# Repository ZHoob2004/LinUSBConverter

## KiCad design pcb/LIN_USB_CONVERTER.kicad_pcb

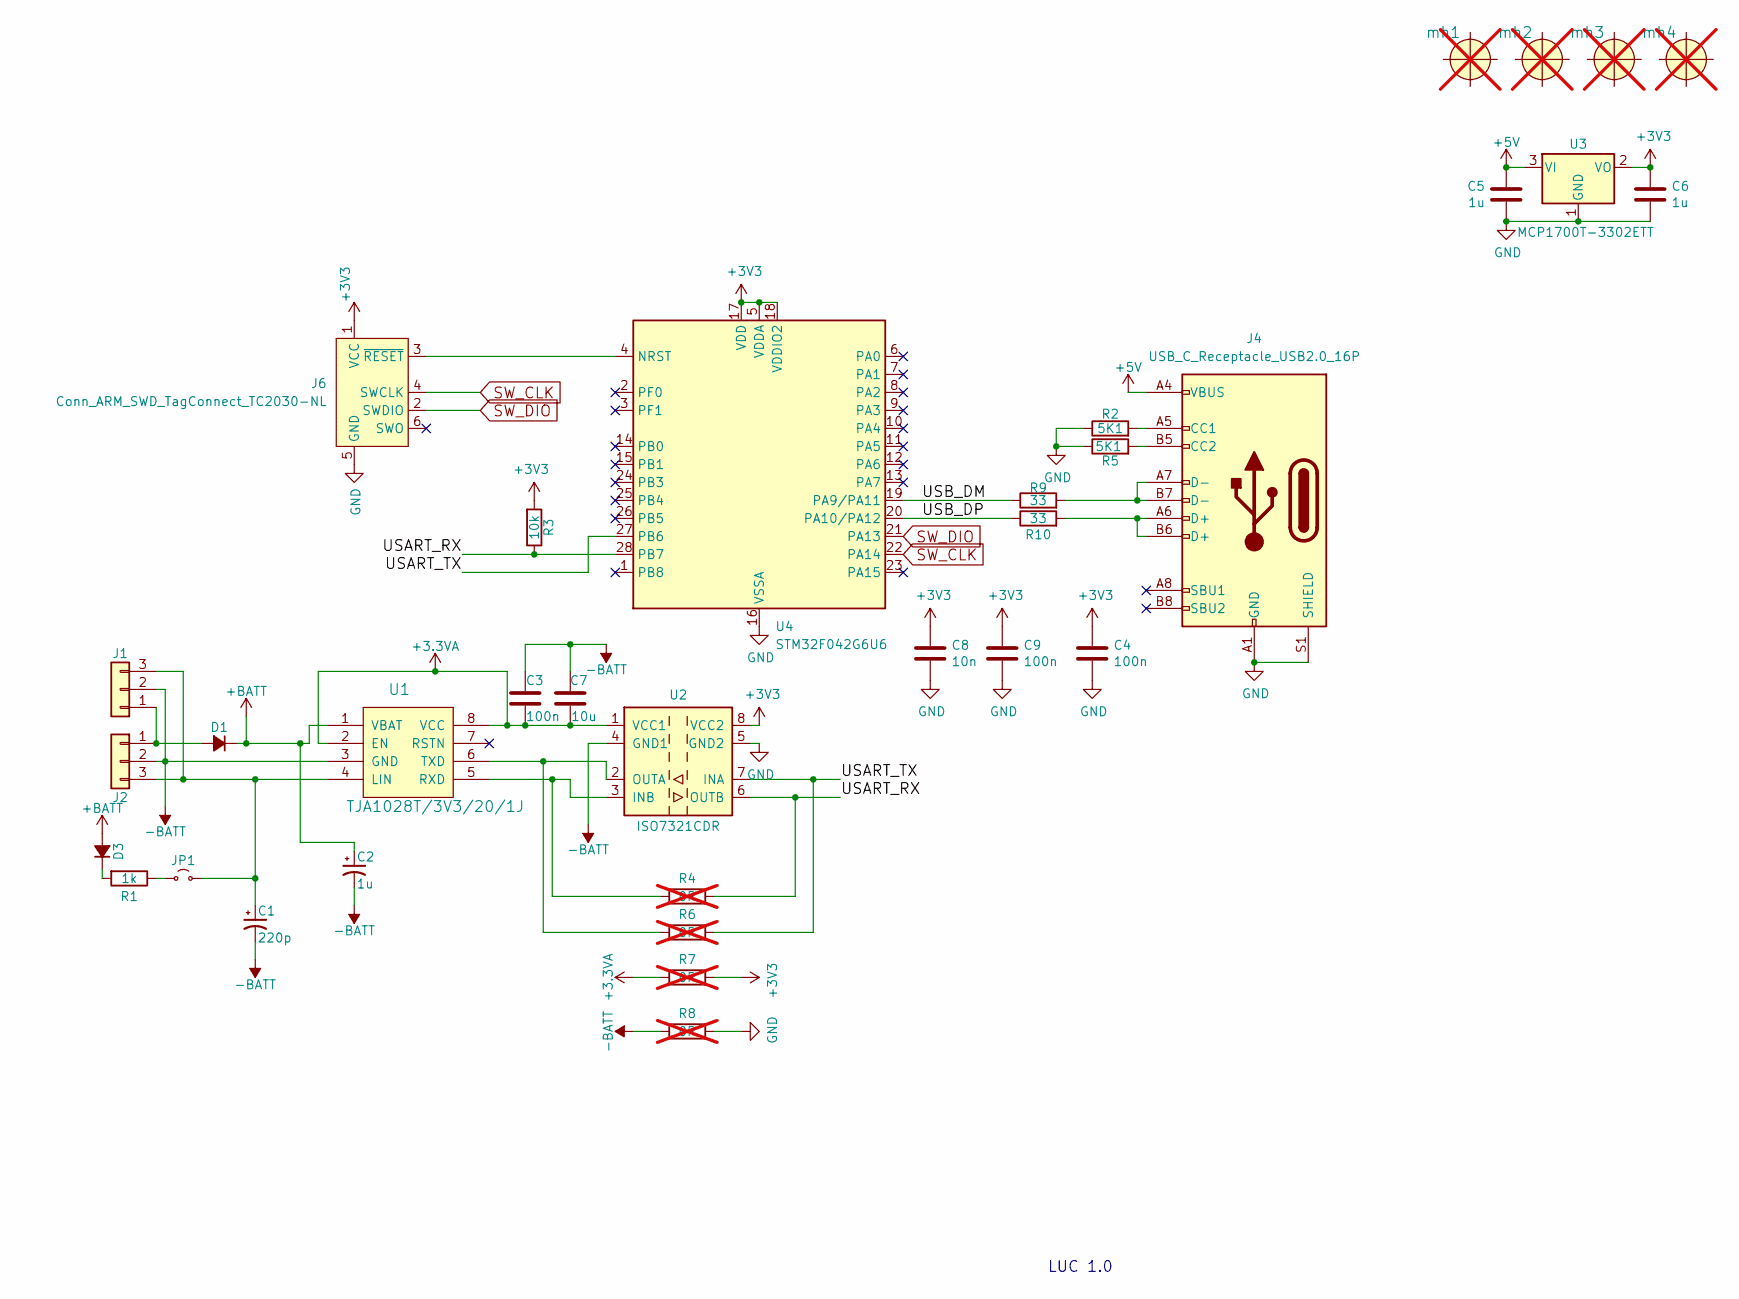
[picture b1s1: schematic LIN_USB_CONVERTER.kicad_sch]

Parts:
C1: 220p; C_0603_1608Metric; LCSC Part # C1603
C2, C5, C6: 1u; C_0603_1608Metric; LCSC Part # C15849
C3, C4, C9: 100n; C_0603_1608Metric; LCSC Part # C14663
C7: 10u; C_0805_2012Metric; LCSC Part # C440198
C8: 10n; C_0603_1608Metric; LCSC Part # C57112
D1, D3: BAV70; SOT-23; LCSC Part # C68978
J1: Conn_01x03; PinHeader_1x03_P2.54mm_Vertical; LCSC Part # C49257
J2: TerminalBlock; TerminalBlock_Phoenix_MKDS-1,5-3_1x03_P5.00mm_Horizontal; LCSC Part # C424695
J4: USB_C_Receptacle_USB2.0_16P; USB_C_Receptacle_GCT_USB4105-xx-A_16P_TopMnt_Horizontal; LCSC Part # C2927038
J6: Conn_ARM_SWD_TagConnect_TC2030-NL; Tag-Connect_TC2030-IDC-NL_2x03_P1.27mm_Vertical
JP1: Jumper_2_Small_Open; SolderJumper-2_P1.3mm_Open_TrianglePad1.0x1.5mm
R1: 1k; R_0603_1608Metric; LCSC Part # C21190
R2, R5: 5K1; R_0603_1608Metric; LCSC Part # C23186
R3: 10k; R_0603_1608Metric; LCSC Part # C25804
R4, R6, R7, R8: 0R; R_0402_1005Metric; not fitted
R9, R10: 33; R_0603_1608Metric; LCSC Part # C23140
U1: TJA1028T/3V3/20/1J; SO-8_3.9x4.9mm_P1.27mm; LCSC Part # C2671173
U2: ISO7321CDR; SOIC-8_3.9x4.9mm_P1.27mm; LCSC Part # C187919
U3: MCP1700T-3302ETT; SOT-23; LCSC Part # C39051
U4: STM32F042G6U6; QFN-28_4x4mm_P0.5mm; LCSC Part # C961597
mh1, mh2, mh3, mh4: fiducial; 1pin; not fitted

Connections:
+3.3VA: C3.2, C7.2, R7.1, U1.2 (EN), U1.8 (VCC), U2.1 (VCC1)
+3V3: C4.1, C6.1, C8.1, C9.1, J6.1 (VCC), R3.2, R7.2, U2.8 (VCC2), U3.2 (VO), U4.5 (VDDA), U4.17 (VDD), U4.18 (VDDIO2)
+5V: C5.1, J4.A4 (VBUS), J4.A9 (VBUS), J4.B4 (VBUS), J4.B9 (VBUS), U3.3 (VI)
+BATT: C2.1, D1.3 (K), D3.1 (A), U1.1 (VBAT)
-BATT: C1.2, C2.2, C3.1, C7.1, J1.2, J2.2, R8.1, U1.3 (GND), U2.4 (GND1)
/USART_RX: R3.1, R4.2, U2.6 (OUTB), U4.28 (PB7)
/USART_TX: R6.2, U2.7 (INA), U4.27 (PB6)
/USB_DM: R9.1, U4.19 (PA9/PA11)
/USB_DP: R10.1, U4.20 (PA10/PA12)
GND: C4.2, C5.2, C6.2, C8.2, C9.2, J4.A1 (GND), J4.A12 (GND), J4.B1 (GND), J4.B12 (GND), J4.S1 (SHIELD), J6.5 (GND), R2.1, R5.1, R8.2, U2.5 (GND2), U3.1 (GND), U4.16 (VSSA)
unnamed: D1.1 (A), J1.1, J2.1
unnamed: D3.3 (K), R1.2
unnamed: C1.1, J1.3, J2.3, JP1.2 (B), U1.4 (LIN)
unnamed: J4.A5 (CC1), R2.2
unnamed: J4.B5 (CC2), R5.2
unnamed: J4.A6 (D+), J4.B6 (D+), R10.2
unnamed: J4.A7 (D-), J4.B7 (D-), R9.2
unnamed: J6.3 (~RESET), U4.4 (NRST)
unnamed: JP1.1 (A), R1.1
unnamed: R4.1, U1.5 (RXD), U2.3 (INB)
unnamed: R6.1, U1.6 (TXD), U2.2 (OUTA)
SW_CLK: J6.4 (SWCLK), U4.22 (PA14)
SW_DIO: J6.2 (SWDIO), U4.21 (PA13)

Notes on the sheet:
LUC 1.0

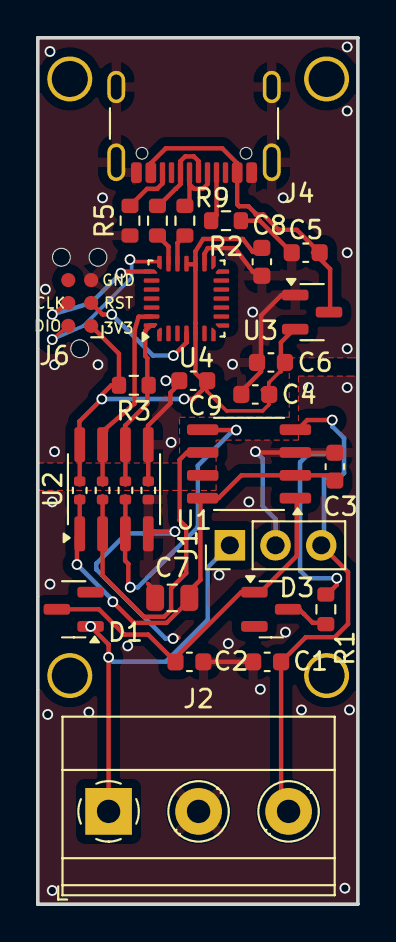
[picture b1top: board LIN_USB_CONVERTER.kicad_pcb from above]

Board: 2 copper layers, 17.8 x 48.1 mm, 34 parts (1 on the bottom side), 23 nets.

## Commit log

2025-07-09 changed to usb-c, tag-connect, and prepared for jlcpcb production
2025-07-14 moved terminals to top, added mounting holes
2025-07-14 final production check, moved vias
2025-07-15 updated to kicad 9.0
2025-07-23 fixed 12v shorted to 3v3
